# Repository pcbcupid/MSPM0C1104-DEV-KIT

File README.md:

# MSPM0C1104-DEV-KIT / INDUSTRIAL TEMPERATURE/HUMIDITY SENSOR MODULE WITH RS485 OUTPUT 

This design can be used as both exploration boards for worlds tiniest controller and also as a stand alone sensor module 
which can measure temperature and humidity with very high prescision. 

You can read more about it here : [link](https://learn.pcbcupid.com/boards/g-sense/hdc3020-rs485)

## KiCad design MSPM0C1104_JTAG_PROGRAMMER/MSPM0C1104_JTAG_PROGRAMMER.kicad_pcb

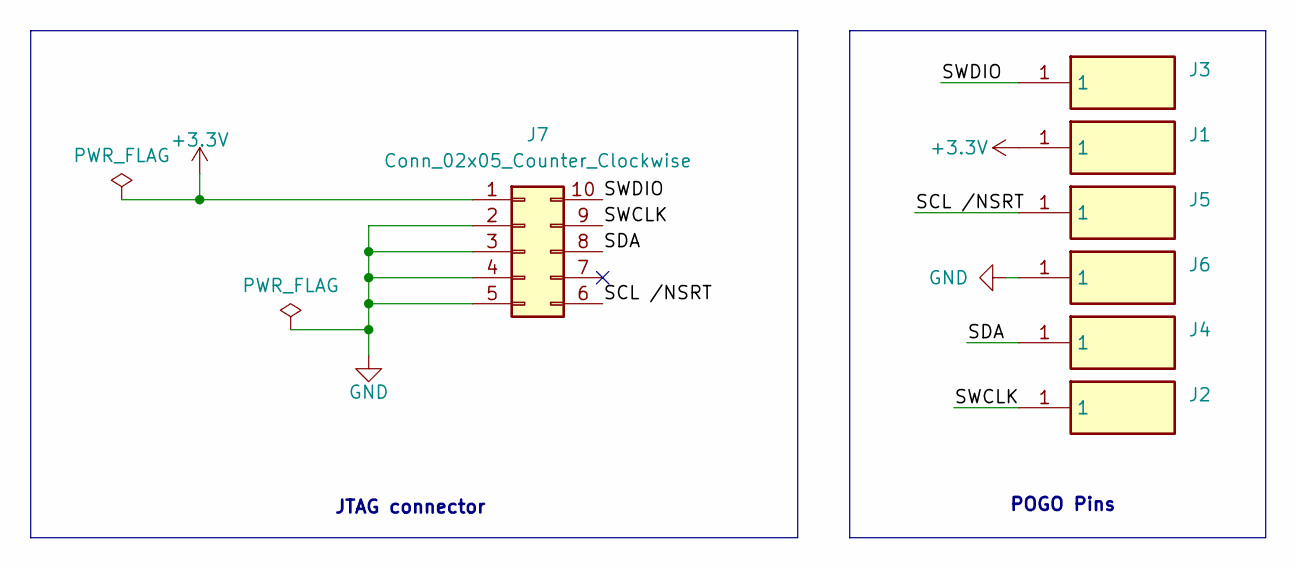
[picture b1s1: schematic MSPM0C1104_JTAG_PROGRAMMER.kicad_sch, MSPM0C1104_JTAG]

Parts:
J1, J2, J3, J4, J5, J6: 0950-0-15-20-64-14-11-0; TestPoint_THTPad_D1.5mm_Drill1mm; Mouser Part Number 575-950015206414110
J7: Conn_02x05_Counter_Clockwise; PinSocket_2x05_P2.54mm_Vertical

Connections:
+3.3V: J1.1, J7.1
/SCL /NSRT: J5.1, J7.6
/SDA: J4.1, J7.8
/SWCLK: J2.1, J7.9
/SWDIO: J3.1, J7.10
GND: J6.1, J7.2, J7.3, J7.4, J7.5

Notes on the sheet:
POGO Pins
JTAG connector

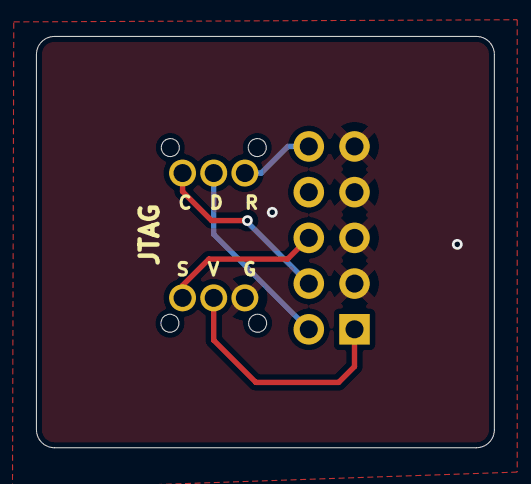
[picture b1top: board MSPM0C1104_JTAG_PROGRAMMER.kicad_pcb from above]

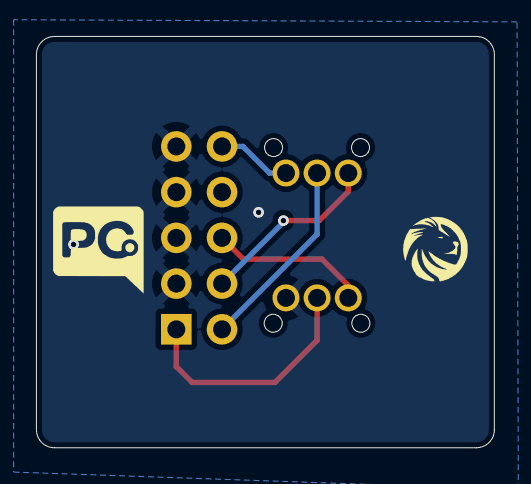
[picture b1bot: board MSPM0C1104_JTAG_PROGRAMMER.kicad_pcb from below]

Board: 2 copper layers, 25.4 x 22.8 mm, 7 parts (6 on the bottom side), 6 nets.

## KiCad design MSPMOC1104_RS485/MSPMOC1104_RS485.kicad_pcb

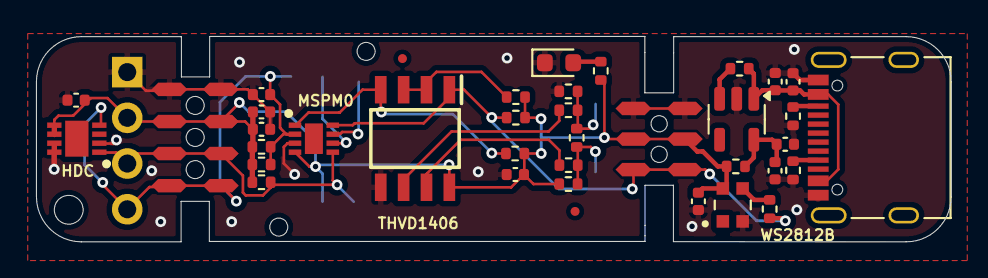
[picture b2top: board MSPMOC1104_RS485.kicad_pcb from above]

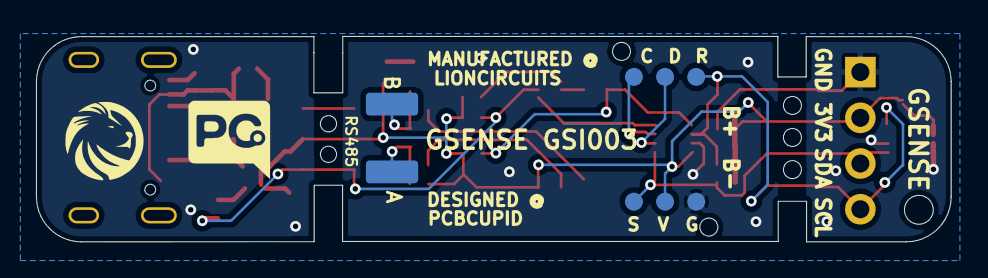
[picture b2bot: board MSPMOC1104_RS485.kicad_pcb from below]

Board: 2 copper layers, 50.8 x 11.4 mm, 58 parts (10 on the bottom side), 20 nets.

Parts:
C1, C2, C3, C6, C7: 0.1uF; C_0402_1005Metric
C4: 10nF; C_0402_1005Metric
C5: 10uF; C_0402_1005Metric
C8, C9, C10: 10uf; C_0402_1005Metric
D2: LED; LED_0603_1608Metric
GND: TestPoint_Pad_1.0x1.0mm
GND#2, GND#3, GND#4, GND#5, GND#6, GND#7, GND#8, GND#9, GND#10, GND#11, GND#12, GND#13, GND#14: TestPoint_Pad_1.0x1.0mm
IC1: HDC3020DEFR
IC2: THVD1426DR
J1, J2, J3, J4, J5, J6: 0950-0-15-20-64-14-11-0; TestPoint_Pad_D1.0mm
J7: USB_C_Receptacle_USB2.0_16P; USB_C_Receptacle_Palconn_UTC16-G
J8: Conn_01x02_Pin; conn_1_2
J9: Conn_01x04; PinHeader_1x04_P2.54mm_Vertical
Lion_circuits-1: LOGO; Lion_circuits_Logo
PCB_CUBID-1: LOGO; PCB_CUBID
R1: 220R; R_0402_1005Metric
R2, R3: 4.7K; R_0402_1005Metric
R4, R6: 5.1k; R_0402_1005Metric
R5: 47K; R_0402_1005Metric
R7, R8, R9, R12, R14, R17: 4.7k; R_0402_1005Metric
R10, R11: 100; R_0402_1005Metric
R13: 120E; R_0402_1005Metric
R15: 100K; R_0402_1005Metric
R16: 0R; R_0402_1005Metric
U1: WS2812-2020; LED_WS2812-2020
U2: MSPM0C1104SDSGR
U3: AP2112K-3.3v; SOT-23-5

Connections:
+3.3V: C1.1, C2.1, C3.1, C5.1, C7.1, GND.1, GND#7.1, GND#8.1, GND#10.1, IC1.5 (VDD), IC1.6 (~RESET), IC2.8 (VCC), J1.1, J9.2, R2.1, R3.1, R5.1, R7.1, R8.2, R9.1, R12.2, R16.1, R17.2, U1.4 (VDD), U2.4 (VDD)
/SCL /NSRT: C4.1, GND#11.1, GND#13.1, IC1.4 (SCL), J2.1, J9.4, R3.2, R5.2, U2.2 (PA1/NRST)
/SDA: GND#2.1, GND#14.1, IC1.1 (SDA), J6.1, J9.3, R2.2, U2.5 (PA0)
/SWCLK: J5.1, U2.7 (PA20/A6/SWCLK)
/SWDIO: J3.1, U2.6 (PA19/SWDIO)
/VBUS: C6.1, C10.1, J7.A4 (VBUS), J7.A9 (VBUS), J7.B4 (VBUS), J7.B9 (VBUS), R15.1, U3.1 (VIN)
/cc1: J7.A5 (CC1), R4.1
/cc2: J7.B5 (CC2), R6.1
/led: R1.2, U1.3 (DI)
/pa24: GND#6.1, GND#9.1, IC2.1 (R), R1.1, R9.2, U2.8 (PA24/A3)
/pa27: IC2.4 (D), R8.1, U2.1 (PA27/A0)
/padA: IC2.7 (B), R10.1
/padB: IC2.6 (A), R11.1
/pasA: J8.1, R10.2, R12.1, R13.2
/pasB: J8.2, R11.2, R13.1, R14.2
/rs: IC2.2 (~RE), IC2.3 (~SHDN), R7.2
GND: C1.2, C2.2, C3.2, C4.2, C5.2, C6.2, C7.2, C8.2, C9.2, C10.2, D2.1 (K), GND#3.1, GND#4.1, GND#5.1, GND#12.1, IC1.2 (ADDR), IC1.7 (ADDR1), IC1.8 (GND), IC2.5 (GND), J4.1, J7.A1 (GND), J7.A12 (GND), J7.B1 (GND), J7.B12 (GND), J9.1, R4.2, R6.2, R14.1, U1.2 (GND), U2.3 (VSS), U3.2 (GND)
unnamed: D2.2 (A), R17.1
unnamed: R15.2, U3.3 (EN)
unnamed: C8.1, C9.1, R16.2, U3.5 (VOUT)

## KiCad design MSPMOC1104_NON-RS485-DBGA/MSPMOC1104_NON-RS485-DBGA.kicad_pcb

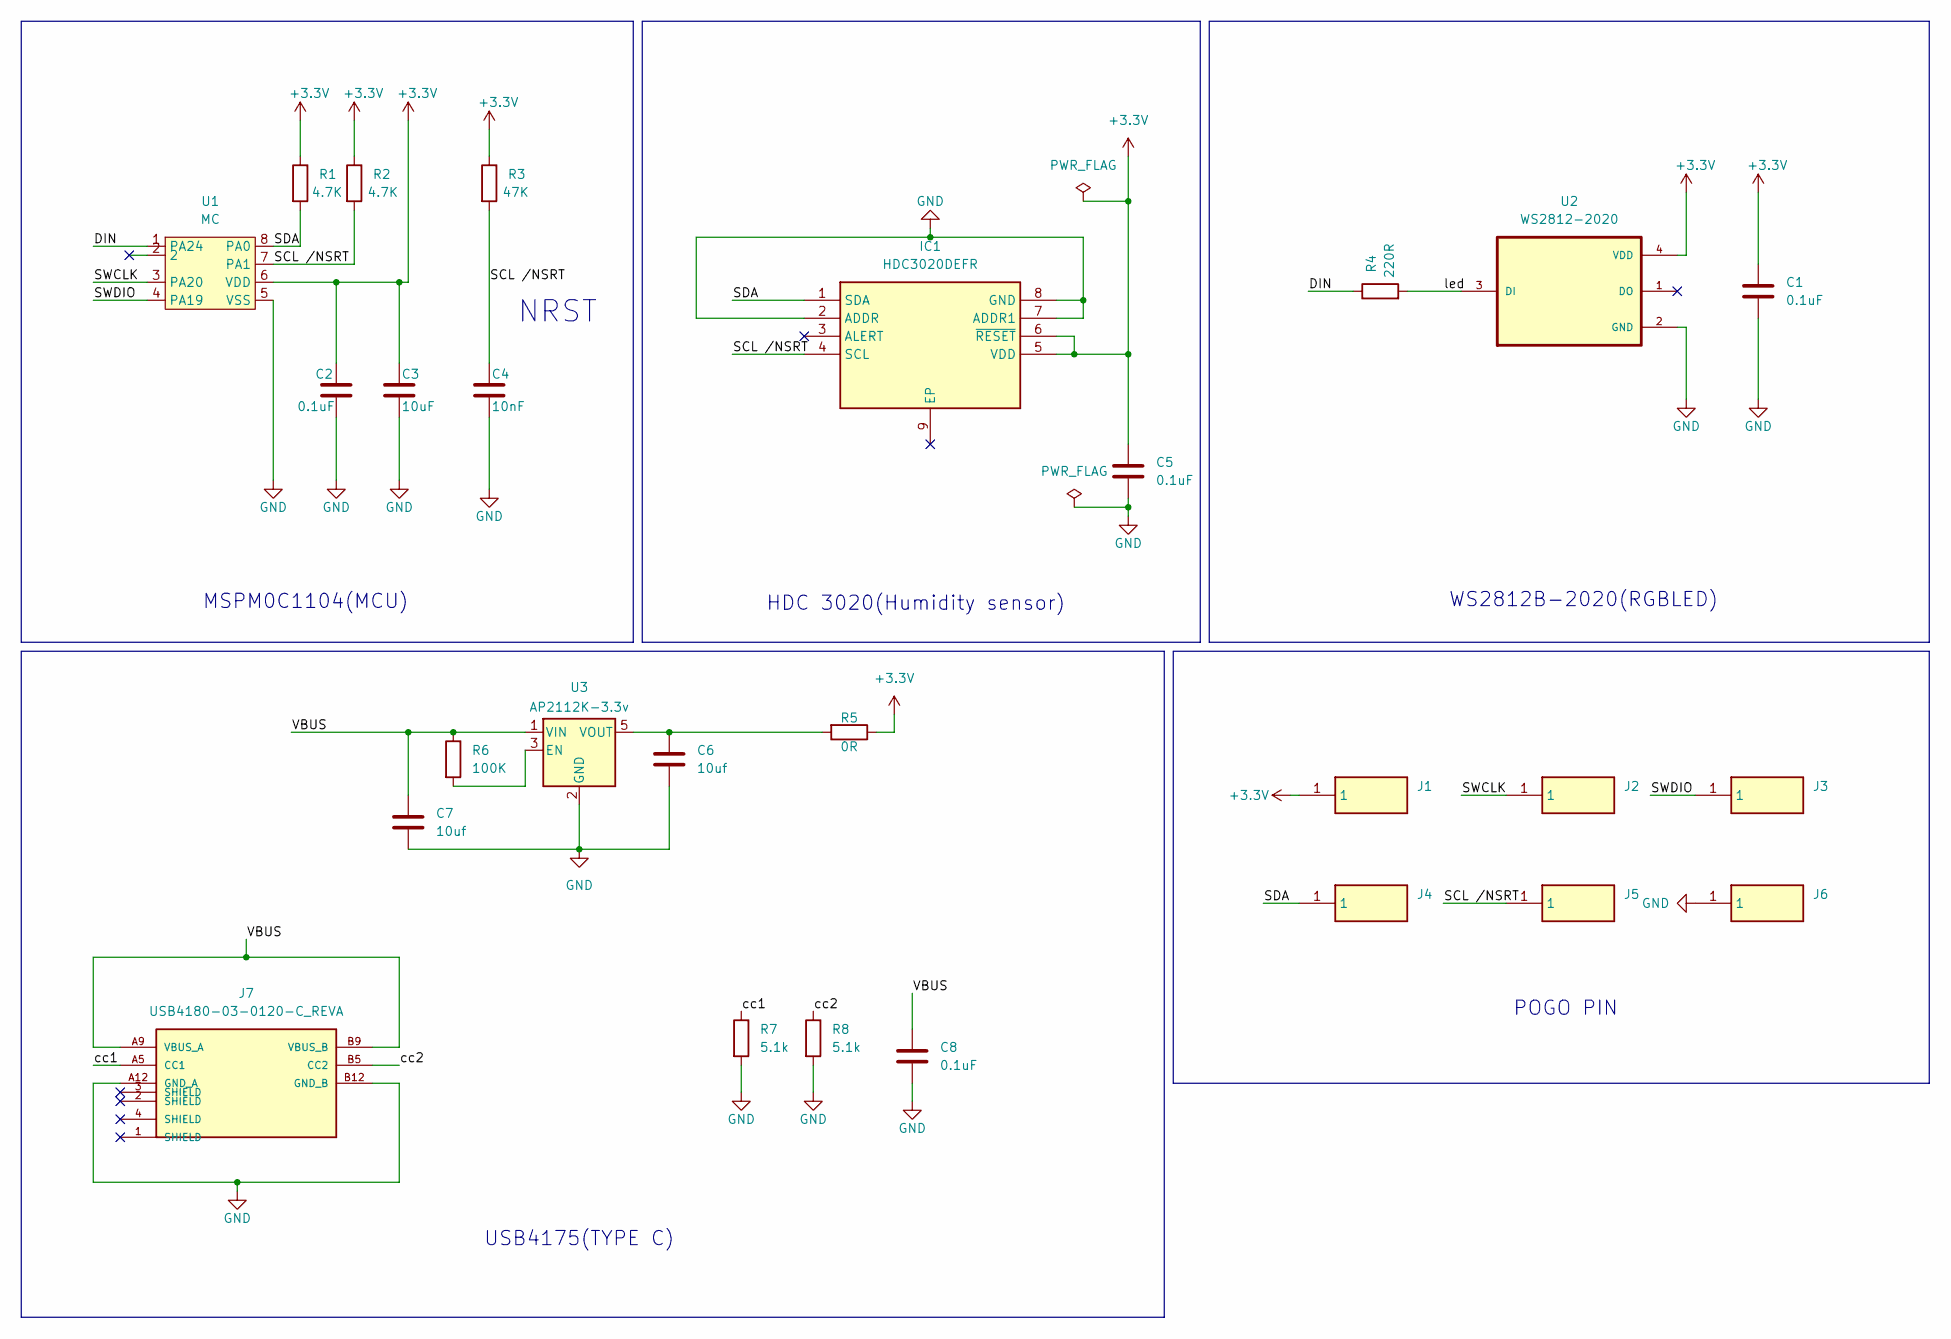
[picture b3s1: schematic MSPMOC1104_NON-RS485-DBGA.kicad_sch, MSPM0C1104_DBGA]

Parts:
C1, C2, C5, C8: 0.1uF; C_0201_0603Metric_Pad0.64x0.40mm_HandSolder
C3: 10uF; C_0201_0603Metric_Pad0.64x0.40mm_HandSolder
C4: 10nF; C_0201_0603Metric_Pad0.64x0.40mm_HandSolder
C6, C7: 10uf; C_0201_0603Metric_Pad0.64x0.40mm_HandSolder
IC1: HDC3020DEFR; Mouser Part Number 595-HDC3020DEFR
J1, J2, J3, J4, J5, J6: 0950-0-15-20-64-14-11-0; TestPoint_Pad_D1.0mm; Mouser Part Number 575-950015206414110
J7: USB4180-03-0120-C_REVA; USB4180030120C; PARTREV A; DigiKey_Part_Number 2073-USB4180-03-0120-CTR-ND
R1, R2: 4.7K; R_0201_0603Metric_Pad0.64x0.40mm_HandSolder
R3: 47K; R_0201_0603Metric_Pad0.64x0.40mm_HandSolder
R4: 220R; R_0201_0603Metric_Pad0.64x0.40mm_HandSolder
R5: 0R; R_0201_0603Metric_Pad0.64x0.40mm_HandSolder
R6: 100K; R_0201_0603Metric_Pad0.64x0.40mm_HandSolder
R7, R8: 5.1k; R_0201_0603Metric_Pad0.64x0.40mm_HandSolder
U1: MC; MCU_TI_MSPM0C1104
U2: WS2812-2020; LED_WS2812-2020; PARTREV V1.3
U3: AP2112K-3.3v; SOT-23-5

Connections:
+3.3V: C1.1, C2.1, C3.1, C5.1, IC1.5 (VDD), IC1.6 (~RESET), J1.1, R1.1, R2.1, R3.1, R5.1, U1.6 (VDD), U2.4 (VDD)
/DIN: R4.1, U1.1 (PA24)
/SCL /NSRT: C4.1, IC1.4 (SCL), J5.1, R2.2, R3.2, U1.7 (PA1)
/SDA: IC1.1 (SDA), J4.1, R1.2, U1.8 (PA0)
/SWCLK: J2.1, U1.3 (PA20)
/SWDIO: J3.1, U1.4 (PA19)
/VBUS: C7.1, C8.1, J7.A9 (VBUS_A), J7.B9 (VBUS_B), R6.1, U3.1 (VIN)
/cc1: J7.A5 (CC1), R7.1
/cc2: J7.B5 (CC2), R8.1
/led: R4.2, U2.3 (DI)
GND: C1.2, C2.2, C3.2, C4.2, C5.2, C6.2, C7.2, C8.2, IC1.2 (ADDR), IC1.7 (ADDR1), IC1.8 (GND), J6.1, J7.A12 (GND_A), J7.B12 (GND_B), R7.2, R8.2, U1.5 (VSS), U2.2 (GND), U3.2 (GND)
unnamed: R6.2, U3.3 (EN)
unnamed: C6.1, R5.2, U3.5 (VOUT)

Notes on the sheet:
POGO PIN
USB4175(TYPE C)
NRST
HDC 3020(Humidity sensor)
WS2812B-2020(RGBLED)
MSPM0C1104(MCU)

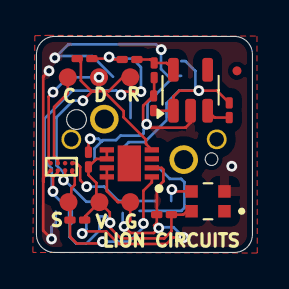
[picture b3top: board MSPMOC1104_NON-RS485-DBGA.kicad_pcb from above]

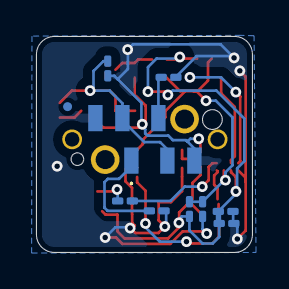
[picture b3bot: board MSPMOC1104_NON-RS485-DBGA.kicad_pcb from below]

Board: 2 copper layers, 12.0 x 12.0 mm, 27 parts (9 on the bottom side), 13 nets.

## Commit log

2025-08-25 updated Kicad files / images

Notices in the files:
MSPM0C1104_JTAG_PROGRAMMER/MSPM0C1104_JTAG_PROGRAMMER.kicad_sch:
License :  CC BY - SA 4.0
